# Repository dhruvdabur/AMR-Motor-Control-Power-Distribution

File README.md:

# AMR-Motor-Control-Power-Distribution

Certainly — here it is in a clear pointer-based format:

## AMR-Motor-Control-Power-Distribution

* A custom-designed PCB that acts as the **central power distribution** and **low-level control unit** of the autonomous mobile robot. 
* Distributes power from the **24V battery** to the robot’s major subsystems, including:

  * **Base motors**
  * **Robotic arm**
  * **Onboard Jetson compute module**
  * **Supporting electronics and sensors** 

## Power Regulation

* Includes **buck converters** to step down the input voltage to the required levels for different subsystems. 
* Provides **stable and regulated power delivery** to components with different voltage requirements.
* Improves overall system efficiency through localized voltage regulation.

## Control Architecture

* Integrates **two electrically isolated STM32F411 microcontrollers**. 
* The microcontrollers are responsible for:

  * **Motor control**
  * **Encoder data handling**
  * **IMU data handling**
  * **Communication with the Jetson compute module** 
* Electrical isolation between control and power sections helps:

  * Reduce electrical noise
  * Improve system reliability
  * Protect sensitive electronics from faults in high-current sections

## Protection and Reliability Features

* Designed with a strong focus on **electrical protection** and **robust operation**. 
* Protection features include:

  * **Galvanic isolation**
  * **Isolated DC-DC converters**
  * **Polyfuses**
  * **TVS diodes** 
* These features help protect the system against:

  * Overcurrent conditions
  * Voltage spikes
  * Electrical noise and transients
* Includes an **emergency kill switch** with **fuse protection** in the main power path for safe and immediate shutdown. 

## System Design Advantages

* Separates **power electronics**, **sensing**, and **computing** into distinct electrical domains. 
* Improves:

  * **Serviceability**
  * **Fault isolation**
  * **Debugging efficiency**
  * **Long-term system reliability**
* Plays a key role in ensuring stable operation of the robot in demanding autonomous applications.

I can also merge this with your **dual-STM isolation scheme** section so the whole README reads in one consistent pointer-based style.

## The Two Brains 

Got it. For a schematic description, pointer-style is better.

You can write it like this:

## Isolation and Communication Architecture

* The board uses **two STM32 microcontrollers** arranged in **separate electrical domains**. 
* The two controllers communicate through **optocouplers**, providing electrical isolation between the domains.
* Communication across the isolation barrier consists of:

  * **1 clock synchronization line**
  * **2 UART lines**
* This arrangement allows reliable data exchange while reducing the effect of electrical noise and preventing fault propagation between subsystems.

## Powering Scheme

* One STM32 is powered using an **isolated DC-DC converter**.
* The other STM32 is powered directly from the **raw power rail**.
* This split power architecture helps isolate sensitive control and sensing electronics from noisy power sections.

## Functional Division Between the Two STM32s

### STM32-1

* Receives **encoder data**
* Sends encoder feedback to the **Jetson**
* Receives **motor actuation commands** from the Jetson through **USB CDC**
* Acts as the main communication bridge to the Jetson

### STM32-2

* Acquires **IMU data**
* Sends IMU data to **STM32-1**

## Data Flow

* **Jetson → STM32-1**: motor actuation commands via USB CDC
* **STM32-2 → STM32-1**: IMU data
* **STM32-1 → Jetson**: encoder data and forwarded IMU data

## Design Benefits

* Clear separation of sensing and control responsibilities
* Reduced electrical interference between domains
* Improved robustness in noisy motor-control environments
* Easier debugging and modular system integration

Here is an even shorter README-style version:

## Dual-STM Isolation Scheme

* Two STM32 microcontrollers are used in separate electrical domains.
* The domains are isolated using optocouplers.
* Cross-domain communication uses **one clock synchronization line** and **two UART lines**.
* One STM32, powered through an isolated DC-DC converter, handles encoder acquisition and Jetson communication over USB CDC for motor commands.
* The second STM32, powered from the raw supply, handles IMU acquisition and sends this data to the first STM32.
* The first STM32 forwards the combined feedback data to the Jetson.

## Switch Layout

* The schematic includes three primary power switches: **Main Kill**, **Arm Kill**, and **Base Kill**.
* The **Main Kill Switch** controls overall system power.
* The **Arm Kill Switch** only disables the arm power domain.
* The **Base Kill Switch** only disables the base power domain.
* The **Jetson remains powered even when the Arm Kill Switch is turned off**, allowing computation and system monitoring to continue independently of the arm power domain.

## Fuse Layout and Protection

* The schematic includes **three main fuses on the PCB**:

  * one for the **IMU**
  * one for **each STM32 microcontroller**
* These fuses protect the low-power sensing and control sections of the board.
* In addition, **one fuse may also be added along with each kill switch**, depending on the required level of subsystem protection.
* This design provides better electrical safety and allows faults to be isolated more effectively across different power domains.

You can write it like this:

## High-Current Power Routing

* The high-current section of the PCB is laid out as a **separate and clearly defined power zone**.
* This section is designed with **wider copper paths** to support higher current flow with lower resistance.
* Special attention has been given to the **battery input terminal** to improve current-carrying capability.
* In this region, the **solder mask has been removed intentionally** so that additional solder can be added over the copper.
* Adding extra solder increases the effective conductive cross-section and helps the board handle higher current more reliably.
* This layout improves:

  * **current-carrying capacity**
  * **thermal performance**
  * **power delivery reliability** under heavy load

## Acknowledgment and Conclusion

* This project represents the combined effort of the entire electronics team and all the members who contributed to making this AMR possible.
* The development of the AMR-Motor-Control-Power-Distribution board was made possible through continuous design, testing, debugging, and integration across multiple subsystems.
* Special acknowledgment goes to all the members of the electronics system whose work on power distribution, control, sensing, protection, and system integration contributed to the successful realization of this project.
* This board serves as a key part of the robot’s electrical architecture, enabling reliable power delivery, subsystem isolation, and robust low-level control.
* With this work, the project establishes a strong foundation for stable and scalable operation of the autonomous mobile robot.

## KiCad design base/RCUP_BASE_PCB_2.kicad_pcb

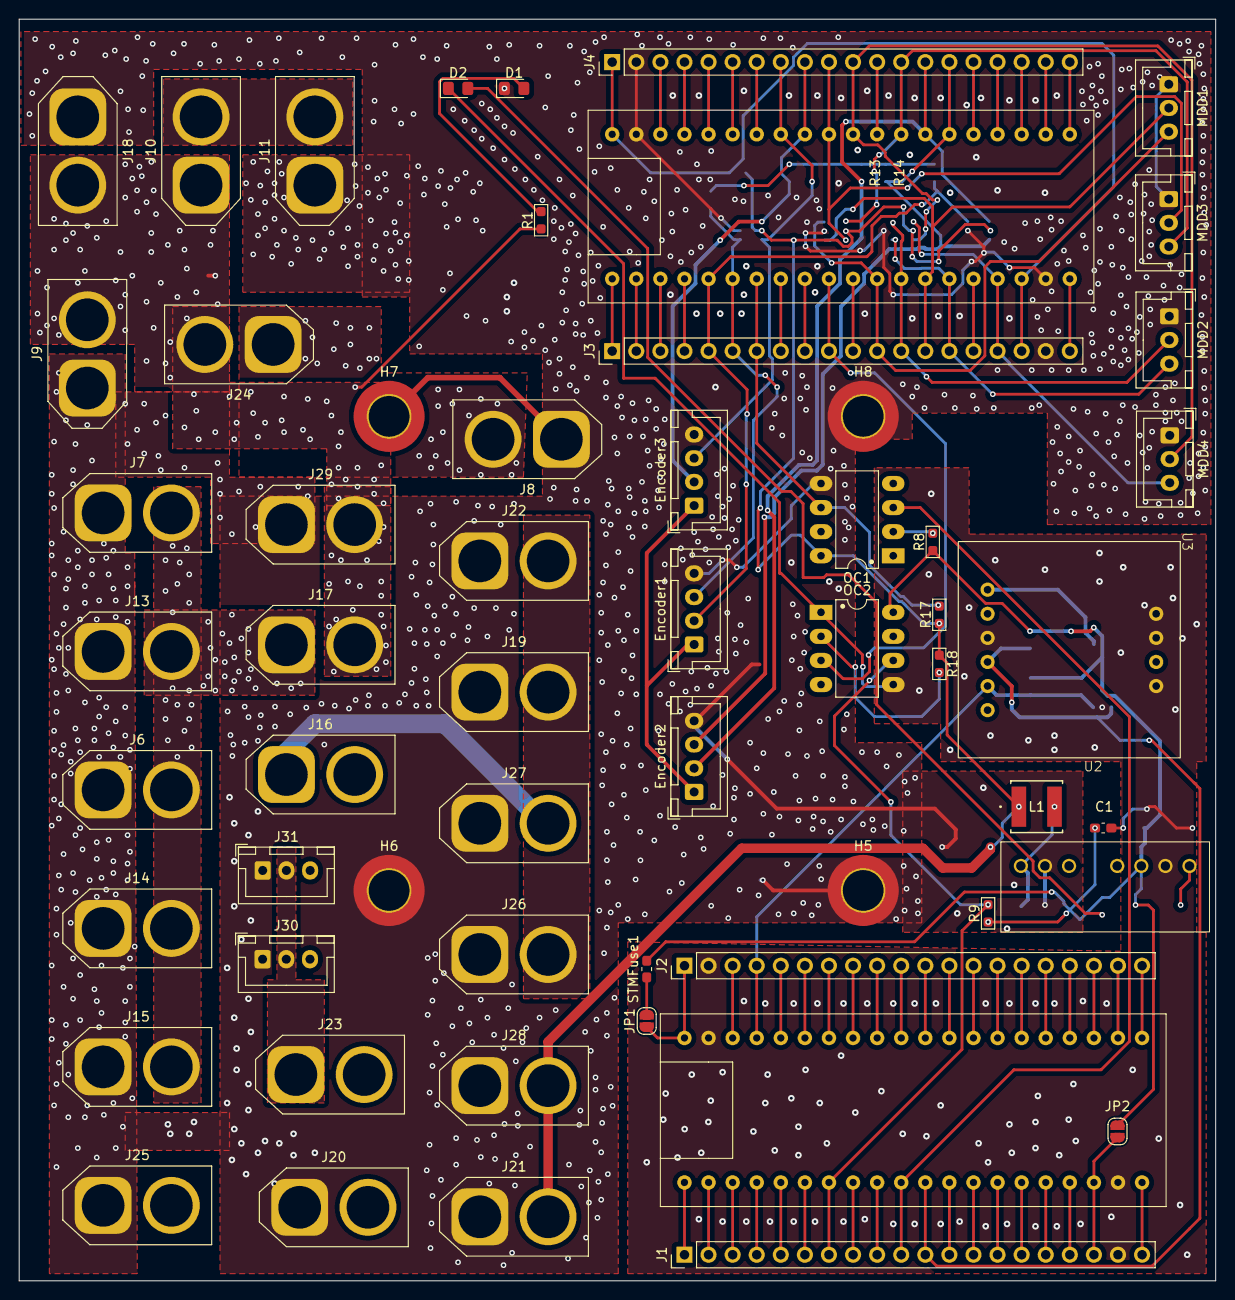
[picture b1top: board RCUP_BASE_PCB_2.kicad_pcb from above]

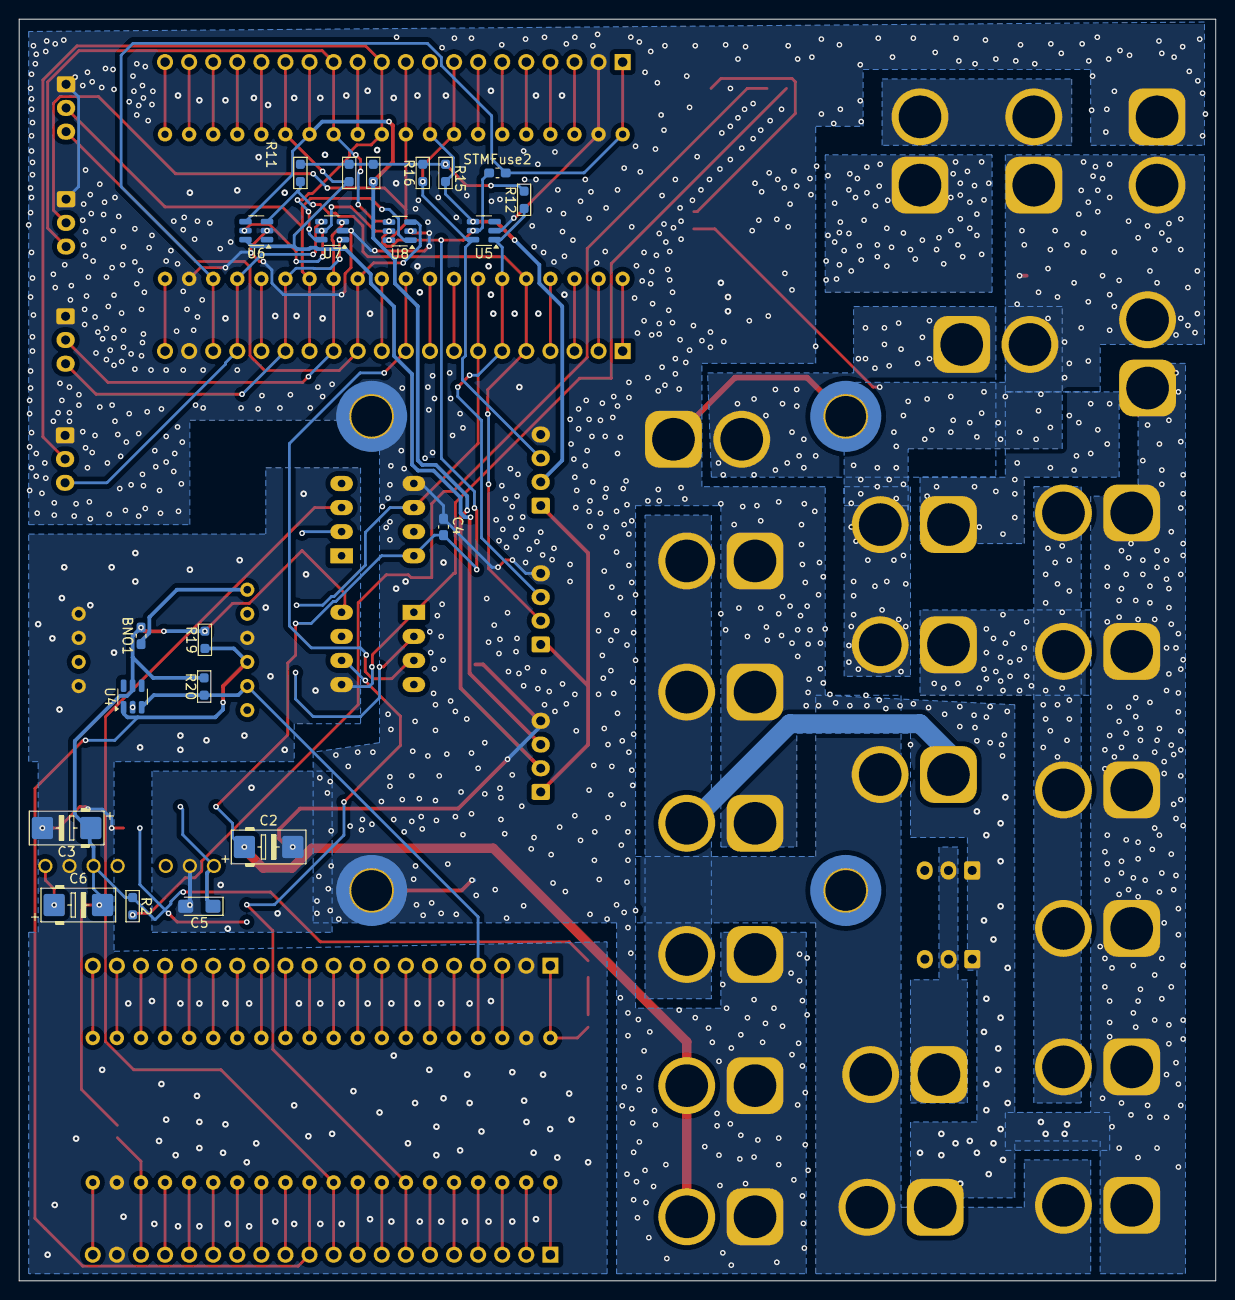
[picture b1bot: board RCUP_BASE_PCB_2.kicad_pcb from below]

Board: 2 copper layers, 126.2 x 133.1 mm, 79 parts (21 on the bottom side), 46 nets.

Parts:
BNO1: Polyfuse; Fuse_0603_1608Metric_Pad1.05x0.95mm_HandSolder
C1, C4: 0.1µ; C_0603_1608Metric_Pad1.08x0.95mm_HandSolder
C2, C3: 100µ; CP_EIA-6032-28_Kemet-C_Pad2.25x2.35mm_HandSolder
C5: 47µ; CP_EIA-3216-18_Kemet-A_HandSolder
C6: 10µ; CP_EIA-6032-28_Kemet-C_Pad2.25x2.35mm_HandSolder
D1, D2: LED; D_0805_2012Metric_Pad1.15x1.40mm_HandSolder
Encoder1, Encoder2, Encoder3: Conn_01x04_Pin; JST_XH_B4B-XH-A_1x04_P2.50mm_Vertical
H5, H6, H7, H8: MountingHole_Pad; MountingHole_4.3mm_M4_DIN965_Pad_TopBottom
J1, J2, J3, J4: Conn_01x20_Pin; PinHeader_1x20_P2.54mm_Vertical
J6: MOTOR 1 PWR; xt60
J7: MOTOR 3 PWR; xt60
J8: STEPPER AND BLDC POWER; xt60
J9: JETSON POWER; xt60
J10: MAIN KILL SWITCH; xt60
J11: BatteryIN; xt60
J13: MOTOR 2 PWR; xt60
J14: MOTOR 4 PWR; xt60
J15: 24V TO 5V BUCK IN; xt60
J16: BASE KILL SWITCH 12V; xt60
J17: BASE KILL SWITCH 24V; xt60
J18: 24V TO 12V BUCK IN; xt60
J19, J20, J25, J26: COOLING SYSTEM; xt60
J21: 24V TO 5V BUCK OUT; xt60
J22: 24V TO 12V BUCK OUT; xt60
J23: ARM KILL SWITCH 12V; xt60
J24: ARM KILL SWITCH; xt60
J27: EXTRA 12V PORT; xt60
J28: EXTRA 5V PORT; xt60
J29: EXTRA 24V PORT; xt60
J30, J31: Conn_01x03_Pin; JST_XH_B3B-XH-A_1x03_P2.50mm_Vertical
JP1, JP2: SolderJumper_2_Open; SolderJumper-2_P1.3mm_Open_RoundedPad1.0x1.5mm
L1: 4.7µ; IND_SWPA5040S_SNL-M
MDD1, MDD2, MDD3, MDD4: Conn_01x03_Pin; JST_XH_B3B-XH-A_1x03_P2.50mm_Vertical
MotorController1, MotorController2: STM32F411_BP; STM32F411-BP
OC1, OC2: 6N137; DIP-8_W7.62mm_LongPads
R1: 1K; R_0603_1608Metric_Pad0.98x0.95mm_HandSolder
R2: 220; R_0603_1608Metric_Pad0.98x0.95mm_HandSolder
R8, R9, R17, R18: 350; R_0603_1608Metric_Pad0.98x0.95mm_HandSolder
R11, R12, R13, R14, R15, R16: 6R8K; R_0603_1608Metric_Pad0.98x0.95mm_HandSolder
R19, R20: 4R7K; R_0603_1608Metric_Pad0.98x0.95mm_HandSolder
STMFuse1, STMFuse2: Polyfuse; Fuse_0603_1608Metric_Pad1.05x0.95mm_HandSolder
U2: WRB0505S-3WR3
U3: BNO055; 7_semi_BNO055
U4, U5, U6, U7, U8: USBLC6-4SC6; SOT-23-6

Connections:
3.3V_STM_1: J2.3, MotorController1.3 (3V3)
3.3V_STM_2: J4.3, MotorController2.3 (3V3)
5V: C2.1, C4.1, J21.P (POS), J28.P (POS), L1.1, OC1.8 (VCC), R17.1, R18.1, STMFuse2.1, U5.5 (VBUS), U6.5 (VBUS), U7.5 (VBUS), U8.5 (VBUS)
5VIn: Encoder1.1, Encoder2.1, Encoder3.1
5V_ISO: BNO1.2, C1.1, C3.1, C6.2, JP2.1 (A), OC2.8 (VCC), R2.1, R8.1, R9.1, R19.2, R20.2, STMFuse1.2, U2.5 (+vo), U4.5 (VBUS)
5V_ISO_BNO: BNO1.1, U3.1 (Vin)
5V_ISO_FUSE_OUT: JP1.2 (B), STMFuse1.1
5V_NON_ISO: R11.2, R12.2, R13.2, R14.2, R15.2, R16.2
5V_NON_ISO_IN: J3.18, J4.1, MotorController2.1 (5V), MotorController2.38 (5V), STMFuse2.2
12V: J16.P (POS), J19.P (POS), J20.P (POS), J22.P (POS), J23.P (POS), J25.P (POS), J26.P (POS)
12V_ARM: J23.N (NEG), J30.2, J31.2
12V_BASE: J16.N (NEG), J27.P (POS)
24V: J9.P (POS), J10.N (NEG), J17.P (POS), J18.P (POS), J24.P (POS), J29.P (POS), R1.1
24V_ARM: J8.P (POS), J24.N (NEG)
24V_BASE: J6.P (POS), J7.P (POS), J13.P (POS), J14.P (POS), J15.P (POS), J17.N (NEG)
24V_BATTERY: J10.P (POS), J11.P (POS)
BNO_SCL: J2.4, MotorController1.4 (PB10), R20.1, U3.5 (SCL), U4.3 (I/O2)
BNO_SDA: J1.11, MotorController1.31 (PB3), R19.1, U3.4 (SDA), U4.1 (I/O1)
ENC1A: Encoder1.2, J3.5, MotorController2.25 (PA8), R11.1, U6.3 (I/O2)
ENC1B: Encoder1.3, J3.6, MotorController2.26 (PA9), R12.1, U5.1 (I/O1)
ENC2A: Encoder2.2, J4.14, MotorController2.14 (PA1), R14.1, U6.4 (I/O3)
ENC2B: Encoder2.3, J4.15, MotorController2.15 (PA0), R13.1, U6.6 (I/O4)
ENC3A: Encoder3.2, J4.9, MotorController2.9 (PA6), R15.1, U5.4 (I/O3)
ENC3B: Encoder3.3, J4.8, MotorController2.8 (PA7), R16.1, U5.6 (I/O4)
GND: C2.2, C4.2, C5.2, D1.1 (K), Encoder1.4, Encoder2.4, Encoder3.4, H5.1, H6.1, H7.1, H8.1, J3.19, J4.2, J6.N (NEG), J7.N (NEG), J8.N (NEG), J9.N (NEG), J11.N (NEG), J13.N (NEG), J14.N (NEG), J15.N (NEG), J18.N (NEG), J19.N (NEG), J20.N (NEG), J21.N (NEG), J22.N (NEG), J25.N (NEG), J26.N (NEG), J27.N (NEG), J28.N (NEG), J29.N (NEG), J30.1, J31.1, MDD1.1, MDD2.1, MDD3.1, MDD4.1, MotorController2.2 (GND), MotorController2.39 (GND), OC1.5 (GND), U2.2 (-vin), U5.2 (GND), U6.2 (GND), U7.2 (GND), U8.2 (GND)
GND1: C1.2, C3.2, D2.1 (K), J1.19, J2.2, MotorController1.2 (GND), MotorController1.39 (GND), OC2.5 (GND), U2.6 (-vo), U3.3 (GND), U3.7 (PS0), U3.8 (PS1), U3.10 (ADD), U4.2 (GND)
M1DIR: J3.12, MDD1.3, MotorController2.32 (PB4), U8.3 (I/O2)
M1PWM: J3.14, MDD1.2, MotorController2.34 (PB6), U8.1 (I/O1)
M2DIR: J3.13, MDD2.2, MotorController2.33 (PB5), U7.3 (I/O2)
M2PWM: J3.15, MDD2.3, MotorController2.35 (PB7), U7.1 (I/O1)
M3DIR: J4.10, MDD3.2, MotorController2.10 (PA5), U8.6 (I/O4)
M3PWM: J4.13, MDD3.3, MotorController2.13 (PA2), U8.4 (I/O3)
M4DIR: J4.11, MDD4.2, MotorController2.11 (PA4), U7.6 (I/O4)
M4PWM: J3.17, MDD4.3, MotorController2.37 (PB9), U7.4 (I/O3)
unnamed: D1.2 (A), R1.2
unnamed: D2.2 (A), R2.2
unnamed: J1.18, JP2.2 (B), MotorController1.38 (5V)
unnamed: J2.1, JP1.1 (A), MotorController1.1 (5V)
unnamed: OC1.2, R8.2
unnamed: OC2.2, R18.2
unnamed: C5.1, L1.2, U2.1 (+vin)
unnamed: C6.1, U2.7 (Cs)
STM1_RX: J1.7, MotorController1.27 (PA10), OC2.6, R9.2
STM1_TX: J1.10, MotorController1.30 (PA15), OC1.3
STM2_RX: J3.7, MotorController2.27 (PA10), OC1.6, R17.2
STM2_TX: J3.10, MotorController2.30 (PA15), OC2.3

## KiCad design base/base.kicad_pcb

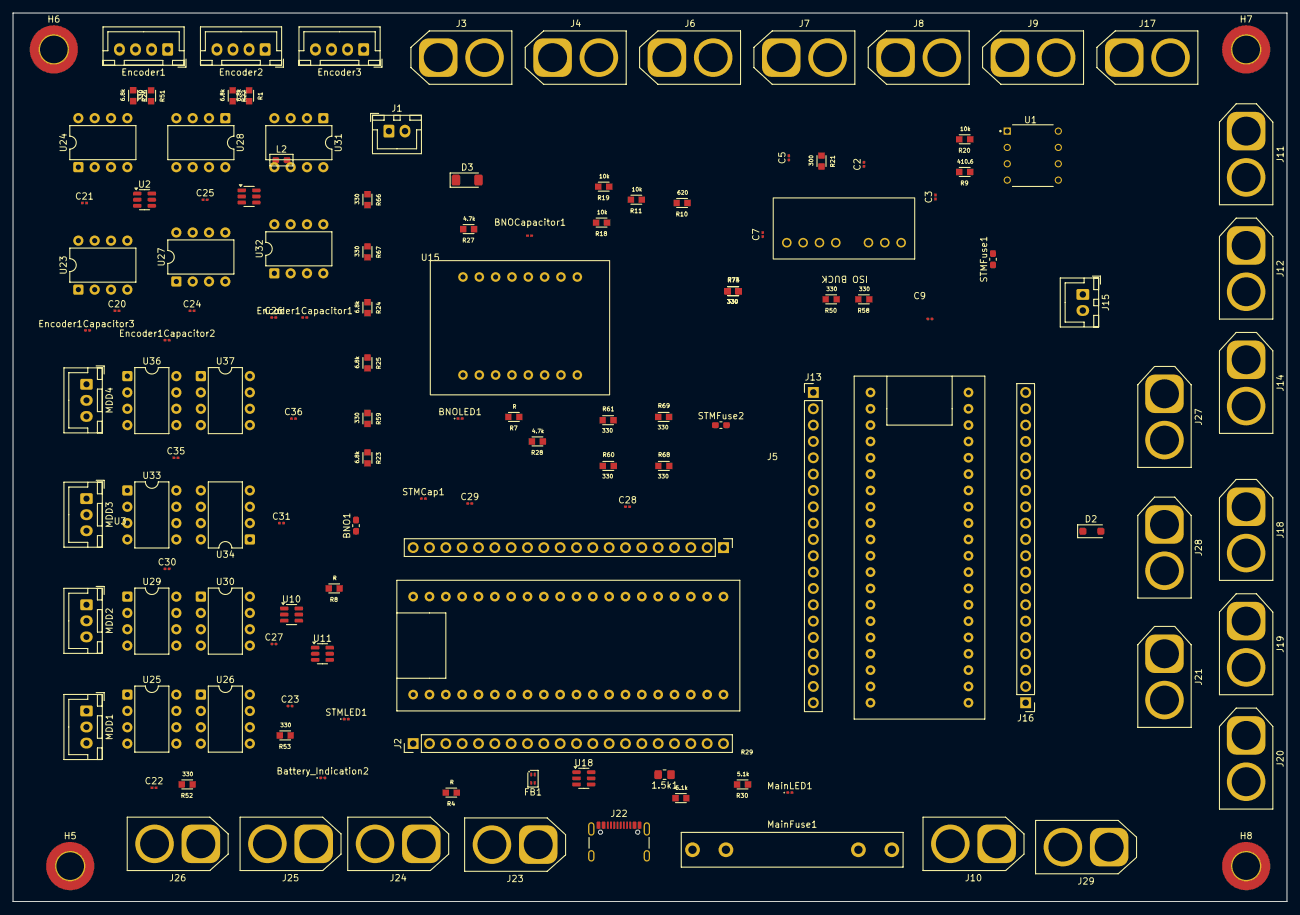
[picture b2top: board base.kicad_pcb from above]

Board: 2 copper layers, 198.1 x 138.2 mm, 135 parts (0 on the bottom side), 114 nets, no tracks yet.

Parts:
1.5k1: 1.5k; R_0805_2012Metric_Pad1.20x1.40mm_HandSolder
BNO1: Polyfuse; Fuse_0603_1608Metric_Pad1.05x0.95mm_HandSolder
BNOCapacitor1: 10uF; C_0201_0603Metric
BNOLED1: LED; LED_0201_0603Metric
Battery_Indication2: LED; LED_0201_0603Metric
C2, C9: 100µ; C_0201_0603Metric
C3: 47n; C_0201_0603Metric
C5: 47µ; C_0201_0603Metric
C7: 10µ; C_0201_0603Metric
C20, C21, C22, C23, C24, C25, C26, C27, C28, C29, C30, C31, C35, C36: 0.1µ; C_0201_0603Metric
D2: RB160M (1 A diode); D_SOD-123F
D3: BZV55B12; D_MiniMELF
Encoder1, Encoder2, Encoder3: Conn_01x04_Pin; JST_XH_B4B-XH-A_1x04_P2.50mm_Vertical
Encoder1Capacitor1, Encoder1Capacitor2, Encoder1Capacitor3: 10uF; C_0201_0603Metric
FB1: FerriteBead; L_CommonModeChoke_Coilcraft_0603USB
H5, H6, H7, H8: MountingHole_Pad; MountingHole_4.3mm_M4_DIN965_Pad_TopBottom
J1: 24V_PINOUTS_ARM; JST_XH_B2B-XH-A_1x02_P2.50mm_Vertical
J2, J5, J13, J16: Conn_01x20_Pin; PinHeader_1x20_P2.54mm_Vertical
J3, J6: BASE_KILL_SWITCH; AMASS_XT60-M_1x02_P7.20mm_Vertical
J4, J18: EXTRA_PORT; AMASS_XT60-M_1x02_P7.20mm_Vertical
J7, J9, J10, J11, J12: 12V_BUCK_PINOUTS_ARM; AMASS_XT60-M_1x02_P7.20mm_Vertical
J8: 24V_PINOUTS_ARM; AMASS_XT60-M_1x02_P7.20mm_Vertical
J14: JETSON_POWER; AMASS_XT60-M_1x02_P7.20mm_Vertical
J15: 12V_BUCK_PINOUTS_ARM; JST_XH_B2B-XH-A_1x02_P2.50mm_Vertical
J17, J28: BuckOut; AMASS_XT60-M_1x02_P7.20mm_Vertical
J19, J21: KSMain2; AMASS_XT60-M_1x02_P7.20mm_Vertical
J20: BatteryIn2; AMASS_XT60-M_1x02_P7.20mm_Vertical
J22: USB_C_Receptacle_USB2.0_14P; USB_C_Receptacle_GCT_USB4105-xx-A_16P_TopMnt_Horizontal
J23: MDDPOWER5; AMASS_XT60-M_1x02_P7.20mm_Vertical
J24: MDDPOWER7; AMASS_XT60-M_1x02_P7.20mm_Vertical
J25: MDDPOWER8; AMASS_XT60-M_1x02_P7.20mm_Vertical
J26: MDDPOWER6; AMASS_XT60-M_1x02_P7.20mm_Vertical
J27, J29: BuckIn; AMASS_XT60-M_1x02_P7.20mm_Vertical
L2: 4.7µ; L_0603_1608Metric_Pad1.05x0.95mm
MDD1, MDD2, MDD3, MDD4: Conn_01x03_Pin; JST_XH_B3B-XH-A_1x03_P2.50mm_Vertical
MainFuse1: Fuse; Fuseholder_Littelfuse_445_030_series_5x30mm
MainLED1: LED; LED_0201_0603Metric
MotorController1, MotorController2: STM32F411_BP; STM32F411-BP
R1, R22, R23, R24, R25, R26: 6.8k; R_0603
R4, R7, R8: R; R_0603
R9: 410.6; R_0603
R10: 620; R_0603
R11, R18, R19, R20: 10k; R_0603
R21: 300; R_0603
R27, R28: 4.7k; R_0603
R29, R30: 5.1k; R_0603
R50, R51, R52, R53, R58, R59, R60, R61, R66, R67, R68, R69, R73, R74: 330; R_0603
STMCap1: 10uF; C_0201_0603Metric
STMFuse1, STMFuse2: Polyfuse; Fuse_0603_1608Metric_Pad1.05x0.95mm_HandSolder
STMLED1: LED; LED_0201_0603Metric
U1: UA741CP; DIP794W45P254L959H508Q8
U2, U3, U10, U11, U18: USBLC6-4SC6; SOT-23-6
U9: WRB0505S-3WR3
U15: BNO055; 7_semi_BNO055
U23, U24, U25, U26, U27, U28, U29, U30, U31, U32, U33, U34, U36, U37: 6N137; DIP-8_W7.62mm

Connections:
5VIn: C22.1, C23.1, C26.1, C27.1, C30.1, C31.1, C35.1, C36.1, R4.2, R52.2, R53.2, R60.2, R61.2, R68.2, R69.2, R73.2, R74.2, U23.2 (A), U24.2 (A), U25.8 (VCC), U26.8 (VCC), U27.2 (A), U28.2 (A), U29.8 (VCC), U30.8 (VCC), U31.2 (A), U32.2 (A), U33.8 (VCC), U34.8 (VCC), U36.8 (VCC), U37.8 (VCC)
5VOut: C2.1, Encoder1.1, Encoder1Capacitor1.1, Encoder1Capacitor2.1, Encoder1Capacitor3.1, Encoder2.1, Encoder3.1, J16.20, L2.1, MotorController2.1 (5V), R1.2, R22.1, R23.2, R24.1, R25.2, R26.1, R27.1, R28.2, U2.5 (VBUS), U3.5 (VBUS), U10.5 (VBUS), U11.5 (VBUS), U18.5 (VBUS)
24V: MainFuse1.2, R9.2, R11.2
BNO_SCL: J5.17, MotorController1.4 (PB10), R27.2, U3.1 (I/O1)
BNO_SDA: J2.11, MotorController1.31 (PB3), R28.1, U2.3 (I/O2)
CTRL: C3.2, D2.2 (A), J2.3, J2.12, MotorController1.23 (PB14), MotorController1.32 (PB4)
Encoder1A: Encoder1.2, R25.1, U3.3 (I/O2), U23.3 (C)
Encoder1AOUT: R50.1, U23.6 (VO)
Encoder1A_OUT: J2.5, MotorController1.25 (PA8)
Encoder1B: Encoder1.3, R26.2, U2.1 (I/O1), U24.3 (C)
Encoder1BOUT: R51.1, U24.6 (VO)
Encoder1B_OUT: J2.6, MotorController1.26 (PA9)
Encoder2A: Encoder2.2, R1.1, U3.4 (I/O3), U27.3 (C)
Encoder2AOUT: R58.1, U27.6 (VO)
Encoder2A_OUT: J5.12, MotorController1.9 (PA6)
Encoder2B: Encoder2.3, R22.2, U3.6 (I/O4), U28.3 (C)
Encoder2BOUT: R59.1, U28.6 (VO)
Encoder2B_OUT: J5.13, MotorController1.8 (PA7)
Encoder3A: Encoder3.2, R23.1, U2.4 (I/O3), U31.3 (C)
Encoder3AOUT: R66.1, U31.6 (VO)
Encoder3A_OUT: J5.6, MotorController1.15 (PA0)
Encoder3B: Encoder3.3, R24.2, U2.6 (I/O4), U32.3 (C)
Encoder3BOUT: R67.1, U32.6 (VO)
Encoder3B_OUT: J5.7, MotorController1.14 (PA1)
GND: BNOLED1.1 (K), Battery_Indication2.1 (K), C2.2, C3.1, C5.2, C22.2, C23.2, C26.2, C27.2, C30.2, C31.2, C35.2, C36.2, D3.2 (A), Encoder1.4, Encoder1Capacitor1.2, Encoder1Capacitor2.2, Encoder1Capacitor3.2, Encoder2.4, Encoder3.4, FB1.2, H5.1, H6.1, H7.1, H8.1, J13.19, J16.19, J22.A1 (GND), J22.A12 (GND), J22.B1 (GND), J22.B12 (GND), MDD1.1, MDD2.1, MDD3.1, MDD4.1, MainLED1.1 (K), MotorController2.2 (GND), MotorController2.39 (GND), R18.1, R19.1, R29.2, R30.2, STMLED1.1 (K), U1.4 (VCC-), U2.2 (GND), U3.2 (GND), U10.2 (GND), U11.2 (GND), U18.2 (GND), U25.5 (GND), U26.5 (GND), U29.5 (GND), U30.5 (GND), U33.5 (GND), U34.5 (GND), U36.5 (GND), U37.5 (GND)
GND1: BNOCapacitor1.2, C9.2, C20.2, C21.2, C24.2, C25.2, C28.2, C29.2, J2.19, J5.19, MotorController1.2 (GND), MotorController1.39 (GND), STMCap1.2, U15.10 (ADD), U23.5 (GND), U24.5 (GND), U27.5 (GND), U28.5 (GND), U31.5 (GND), U32.5 (GND)
MCD+: 1.5k1.2, J2.9, J22.A6 (D+), J22.B6 (D+), MotorController1.29 (PA12), U18.1 (I/O1)
MCD-: J2.8, J22.A7 (D-), J22.B7 (D-), MotorController1.28 (PA11), U18.3 (I/O2)
MDD1DIR: J2.10, MotorController1.30 (PA15), R53.1, U11.3 (I/O2), U26.6 (VO)
MDD1DIR_out: MDD1.3, U26.3 (C)
MDD1PWM: J2.14, MotorController1.34 (PB6), R52.1, U11.1 (I/O1), U25.6 (VO)
MDD1PWM_out: MDD1.2, U25.3 (C)
MDD2DIR: J5.15, MotorController1.6 (PB1), R61.1, U10.3 (I/O2), U30.6 (VO)
MDD2DIR_out: MDD2.2, U30.3 (C)
MDD2PWM: J5.14, MotorController1.7 (PB0), R60.1, U10.1 (I/O1), U29.6 (VO)
MDD2PWM_out: MDD2.3, U29.3 (C)
MDD3DIR: J5.11, MotorController1.10 (PA5), R69.1, U11.6 (I/O4), U34.6 (VO)
MDD3DIR_out: MDD3.2, U34.3 (C)
MDD3PWM: J5.8, MotorController1.13 (PA2), R68.1, U11.4 (I/O3), U33.6 (VO)
MDD3PWM_out: MDD3.3, U33.3 (C)
MDD4DIR: J5.10, MotorController1.11 (PA4), R73.1, U10.6 (I/O4), U36.6 (VO)
MDD4DIR_out: MDD4.2, U36.3 (C)
MDD4PWM: J2.17, MotorController1.37 (PB9), R74.1, U10.4 (I/O3), U37.6 (VO)
MDD4PWM_out: MDD4.3, U37.3 (C)
unnamed: BNOLED1.2 (A), R7.1
unnamed: Battery_Indication2.2 (A), R20.2
unnamed: D2.1 (K), R21.1
unnamed: D3.1 (K), R9.1, R10.2
unnamed: J2.1, MotorController1.21 (PB12)
unnamed: J2.2, MotorController1.22 (PB13)
unnamed: J2.4, MotorController1.24 (PB15)
unnamed: J2.7, MotorController1.27 (PA10)
unnamed: J2.13, MotorController1.33 (PB5)
unnamed: J2.15, MotorController1.35 (PB7)
unnamed: J2.16, MotorController1.36 (PB8)
unnamed: J2.18, MotorController1.38 (5V)
unnamed: J2.20, MotorController1.40 (3V3)
unnamed: J5.1, MotorController1.20 (VBat)
unnamed: J5.2, MotorController1.19 (PC13)
unnamed: J5.3, MotorController1.18 (PC14)
unnamed: J5.4, MotorController1.17 (PC15)
unnamed: J5.5, MotorController1.16 (RST)
unnamed: J5.9, MotorController1.12 (PA3)
unnamed: J5.16, MotorController1.5 (PB2)
unnamed: J5.18, MotorController1.3 (3V3)
unnamed: J13.1, MotorController2.21 (PB12)
unnamed: J13.2, MotorController2.22 (PB13)
unnamed: J13.3, MotorController2.23 (PB14)
unnamed: J13.4, MotorController2.24 (PB15)
unnamed: J13.5, MotorController2.25 (PA8)
unnamed: J13.6, MotorController2.26 (PA9)
unnamed: J13.7, MotorController2.27 (PA10)
unnamed: J13.8, MotorController2.28 (PA11)
unnamed: J13.9, MotorController2.29 (PA12)
unnamed: J13.10, MotorController2.30 (PA15)
unnamed: J13.11, MotorController2.31 (PB3)
unnamed: J13.12, MotorController2.32 (PB4)
unnamed: J13.13, MotorController2.33 (PB5)
unnamed: J13.14, MotorController2.34 (PB6)
unnamed: J13.15, MotorController2.35 (PB7)
unnamed: J13.16, MotorController2.36 (PB8)
unnamed: J13.17, MotorController2.37 (PB9)
unnamed: J13.18, MotorController2.38 (5V)
unnamed: J13.20, MotorController2.40 (3V3)
unnamed: J16.1, MotorController2.20 (VBat)
unnamed: J16.2, MotorController2.19 (PC13)
unnamed: J16.3, MotorController2.18 (PC14)
unnamed: J16.4, MotorController2.17 (PC15)
unnamed: J16.5, MotorController2.16 (RST)
unnamed: J16.6, MotorController2.15 (PA0)
unnamed: J16.7, MotorController2.14 (PA1)
unnamed: J16.8, MotorController2.13 (PA2)
unnamed: J16.9, MotorController2.12 (PA3)
unnamed: J16.10, MotorController2.11 (PA4)
unnamed: J16.11, MotorController2.10 (PA5)
unnamed: J16.12, MotorController2.9 (PA6)
unnamed: J16.13, MotorController2.8 (PA7)
unnamed: J16.14, MotorController2.7 (PB0)
unnamed: J16.15, MotorController2.6 (PB1)
unnamed: J16.16, MotorController2.5 (PB2)
unnamed: J16.17, MotorController2.4 (PB10)
unnamed: J16.18, MotorController2.3 (3V3)
unnamed: J22.A5 (CC1), R29.1
unnamed: J22.B5 (CC2), R30.1
unnamed: FB1.1, J22.S1 (SHIELD)
unnamed: J22.A4 (VBUS), J22.A9 (VBUS), J22.B4 (VBUS), J22.B9 (VBUS)
unnamed: MainLED1.2 (A), R4.1
unnamed: R8.1, STMLED1.2 (A)
unnamed: R10.1, R18.2, U1.3 (IN+)
unnamed: R11.1, R19.2, U1.2 (IN-)
unnamed: R20.1, U1.6 (OUT)
unnamed: C5.1, L2.2
STM5V_ISO: BNO1.2, BNOCapacitor1.1, C7.2, C9.1, C20.1, C21.1, C24.1, C25.1, C28.1, C29.1, R7.2, R8.2, R50.2, R51.2, R58.2, R59.2, R66.2, R67.2, STMCap1.1, STMFuse1.2, STMFuse2.2, U23.8 (VCC), U24.8 (VCC), U25.2 (A), U26.2 (A), U27.8 (VCC), U28.8 (VCC), U29.2 (A), U30.2 (A), U31.8 (VCC), U32.8 (VCC), U33.2 (A), U34.2 (A), U36.2 (A), U37.2 (A)
STM5V_ISO_IN: BNO1.1, J5.20, MotorController1.1 (5V), STMFuse1.1, STMFuse2.1

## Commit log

2025-10-24 fixed labels
2025-10-28 suggested corrections made
2025-10-28 added 0603 footprint
2025-10-29 made a few changes in schematic
2025-10-31 new schematic
2025-10-31 changes to schematic
2025-10-31 changed the whole schematic and organised it
2025-11-01 components placed\
2025-11-01 made the suggested changes
2025-11-03 50% routing done
2025-11-04 1st iteration complete
2025-11-05 2nd iteration 50% done
2025-11-07 2nd iteration done
2025-11-08 2nd iteration fixed
2025-11-08 2nd iterations error fixed
2025-11-09 fixed dfm errors some still left
2025-11-09 fixed some capacitors
2025-12-01 Changes made, snapabble pdb added
2025-12-02 corrected vias and mouse bite
2025-12-02 prasad suggested changes made
2025-12-02 added logo
2025-12-03 stm flipped
2025-12-03 thermal relief
2025-12-04 everything done
2026-01-13 fixed all the previous issues added mpu footprint
2026-01-20 mpu addes made the traces thicker
2026-02-01 routing and stm orientation fixed
2026-02-02 level shifter added
2026-02-05 changes made
2026-02-12 final iteration ready
2026-03-27 Update README with AMR-Motor-Control-Power-Distribution details
    Added detailed description of the AMR-Motor-Control-Power-Distribution board, including its functions, components, and design considerations.
